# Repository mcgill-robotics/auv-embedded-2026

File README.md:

# McGill Robotics AUV Embedded 2026

Welcome to the AUV Embedded 2026 repository! This repository is created and maintained by the 2026 McGill Robotics AUV Electrical team. It serves as a platform for sharing, calibrating, and version-controlling the embedded software we develop for our Autonomous Underwater Vehicle (AUV).

## About Us

We are a dedicated team of students from McGill Robotics, focused on designing and implementing the PCBs and embedded systems that power our underwater robot. Our mission is to enable autonomous navigation and task performance through advanced electrical engineering and software development.

## What You'll Find Here

- **Embedded Software**: Source code and libraries for our AUV's embedded systems.
- **Team Structure**: Information about our team members and roles.
- **Tutorials**: Guides and tutorials on using ROS (Robot Operating System) and Arduino for our projects.

For more detail please visit our [Wiki](https://github.com/mcgill-robotics/auv-embedded-2026/wiki).

## Hydrophone related work 

You will find in the `dev/hydrophone` branch the following folders : 
- `documentation`, documenting the design of the new hydrophone ADC board. The documentation was written using _mkdocs_, and to view it you'll need to 1. clone the repository locally, then install mkdocs using `pip install mkdocs` and finally render the web documentation using `mkdocs serve` _in the `documentation` folder_
- `kicad`, which contains the source files (`ADC.kicad_pro`) for the design of the new ADC board
- `ltspice`, for the LTSPICE simulations of the ADC board signal chain.

If you have any questions regarding the hydrophone board design please contact @Oscar-T24

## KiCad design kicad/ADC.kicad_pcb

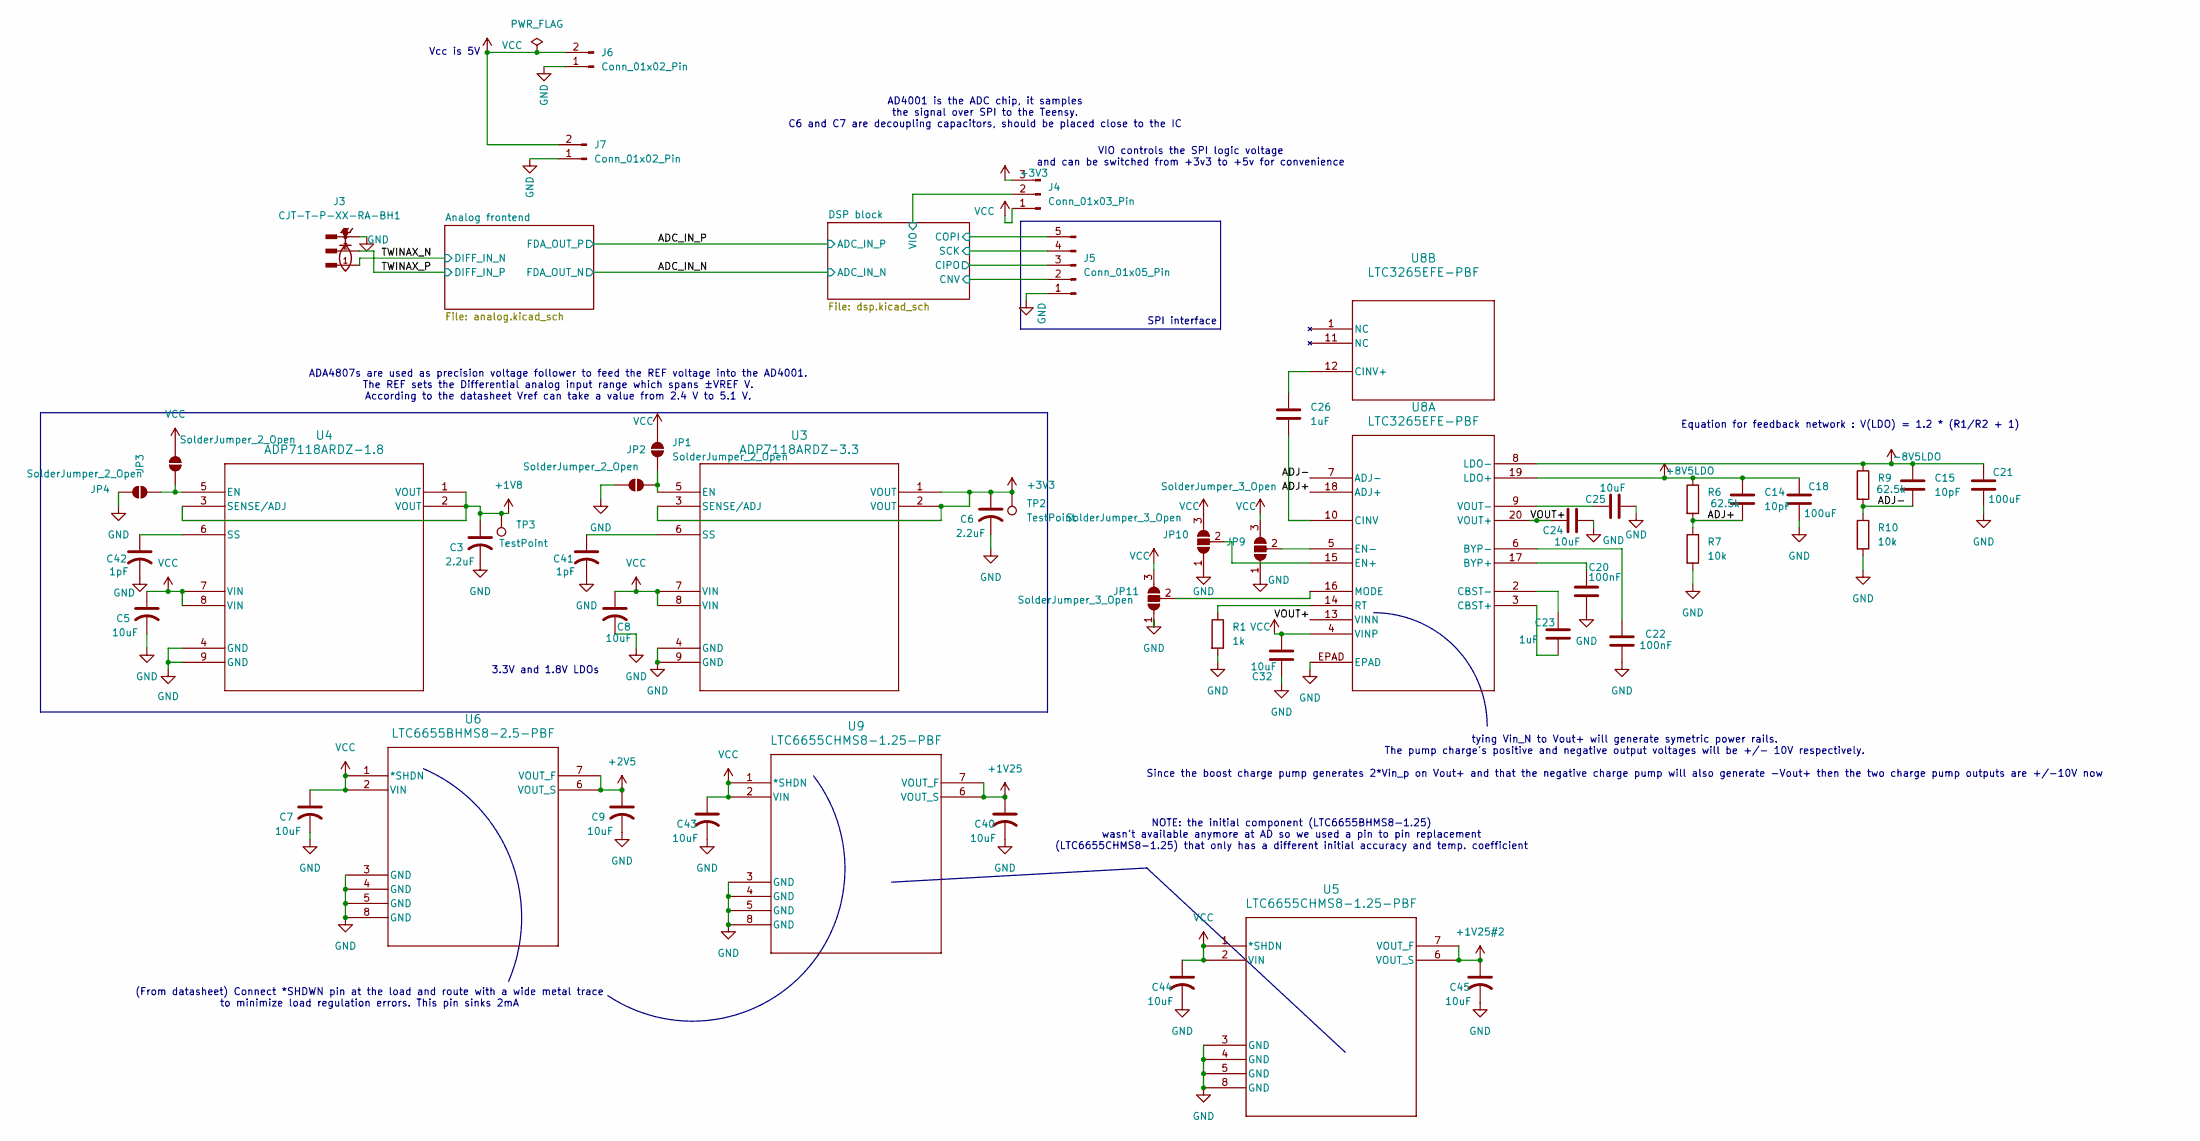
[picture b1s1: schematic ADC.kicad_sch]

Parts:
C3, C6: 2.2uF; C_0603_1608Metric_Pad1.08x0.95mm_HandSolder
C5, C7, C8, C9, C24, C25, C32, C40, C43, C44, C45: 10uF; C_0603_1608Metric_Pad1.08x0.95mm_HandSolder
C14, C15: 10pF; C_0603_1608Metric_Pad1.08x0.95mm_HandSolder
C18, C21: 100uF; C_1206_3216Metric_Pad1.33x1.80mm_HandSolder
C20, C22: 100nF; C_0603_1608Metric_Pad1.08x0.95mm_HandSolder
C23, C26: 1uF; C_0603_1608Metric_Pad1.08x0.95mm_HandSolder
C41, C42: 1pF; C_0603_1608Metric_Pad1.08x0.95mm_HandSolder
J3: CJT-T-P-XX-RA-BH1; SAMTEC_CJT-T-P-XX-RA-BH1; PARTREV E
J4: Conn_01x03_Pin; PinHeader_1x03_P2.54mm_Vertical
J5: Conn_01x05_Pin; PinHeader_1x05_P2.54mm_Vertical
J6, J7: Conn_01x02_Pin; PinHeader_1x02_P2.54mm_Vertical
JP1, JP2, JP3, JP4: SolderJumper_2_Open; SolderJumper-2_P1.3mm_Open_RoundedPad1.0x1.5mm
JP9, JP10, JP11: SolderJumper_3_Open; SolderJumper-3_P1.3mm_Open_RoundedPad1.0x1.5mm_NumberLabels
R1: 1k
R6, R9: 62.5k; R_0603_1608Metric_Pad0.98x0.95mm_HandSolder
R7, R10: 10k; R_0603_1608Metric_Pad0.98x0.95mm_HandSolder
TP2, TP3: TestPoint; TestPoint_Pad_D1.5mm
U3: ADP7118ARDZ-3.3; RD-8-1_ADI
U4: ADP7118ARDZ-1.8; RD-8-1_ADI
U5, U9: LTC6655CHMS8-1.25-PBF; MSOP-8_MS_LIT
U6: LTC6655BHMS8-2.5-PBF; MSOP-8_MS_LIT
U8: LTC3265EFE-PBF; FE_20_ADI

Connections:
+1V8: C3.1, TP3.1 (1_1), U4.1 (VOUT), U4.2 (VOUT), U4.3 (SENSE/ADJ); also elsewhere on the board
+1V25: C40.1, U9.6 (VOUT_S), U9.7 (VOUT_F); also elsewhere on the board
+1V25#2: C45.1, U5.6 (VOUT_S), U5.7 (VOUT_F); also elsewhere on the board
+2V5: C9.1, U6.6 (VOUT_S), U6.7 (VOUT_F); also elsewhere on the board
+3V3: C6.1, J4.3, TP2.1 (1_1), U3.1 (VOUT), U3.2 (VOUT), U3.3 (SENSE/ADJ)
+8V5LDO: C14.1, C18.1, R6.1, U8.19 (LDO+); also elsewhere on the board
-8V5LDO: C15.1, C21.1, R9.1, U8.8 (LDO-); also elsewhere on the board
/ADJ+: C14.2, R6.2, R7.1, U8.18 (ADJ+)
/ADJ-: C15.2, R9.2, R10.1, U8.7 (ADJ-)
/DSP block/CIPO: J5.3; also elsewhere on the board
/DSP block/CNV: J5.2; also elsewhere on the board
/DSP block/COPI: J5.5; also elsewhere on the board
/DSP block/SCK: J5.4; also elsewhere on the board
/DSP block/VIO: J4.2; also elsewhere on the board
/TWINAX_N: J3.1; also elsewhere on the board
/TWINAX_P: J3.2; also elsewhere on the board
/VOUT+: C24.1, U8.13 (VINN), U8.20 (VOUT+)
GND: C3.2, C5.2, C6.2, C7.2, C8.2, C9.2, C18.2, C20.2, C21.2, C22.2, C24.2, C25.2, C32.1, C40.2, C41.2, C42.2, C43.2, C44.2, C45.2, J3.3, J3.4, J3.5, J3.6, J5.1, J6.1, J7.1, JP2.2 (B), JP4.2 (B), JP9.1 (A), JP10.1 (A), JP11.1 (A), R1.2, R7.2, R10.2, U3.4 (GND), U3.9 (GND), U4.4 (GND), U4.9 (GND), U5.3 (GND), U5.4 (GND), U5.5 (GND), U5.8 (GND), U6.3 (GND), U6.4 (GND), U6.5 (GND), U6.8 (GND), U8.EPAD, U9.3 (GND), U9.4 (GND), U9.5 (GND), U9.8 (GND); also elsewhere on the board
unnamed: JP1.1 (A), JP2.1 (A), U3.5 (EN)
unnamed: JP3.2 (B), JP4.1 (A), U4.5 (EN)
unnamed: JP9.2 (C), U8.5 (EN-)
unnamed: JP10.2 (C), U8.15 (EN+)
unnamed: JP11.2 (C), U8.16 (MODE)
unnamed: C41.1, U3.6 (SS)
unnamed: C42.1, U4.6 (SS)
unnamed: C20.1, U8.17 (BYP+)
unnamed: C22.1, U8.6 (BYP-)
unnamed: C23.2, U8.3 (CBST+)
unnamed: C23.1, U8.2 (CBST-)
unnamed: C26.2, U8.10 (CINV)
unnamed: R1.1, U8.14 (RT)
unnamed: C25.1, U8.9 (VOUT-)
unnamed: C26.1, U8.12 (CINV+)
VCC: C5.1, C7.1, C8.1, C32.2, C43.1, C44.1, J4.1, J6.2, J7.2, JP1.2 (B), JP3.1 (A), JP9.3 (B), JP10.3 (B), JP11.3 (B), U3.7 (VIN), U3.8 (VIN), U4.7 (VIN), U4.8 (VIN), U5.1 (*SHDN), U5.2 (VIN), U6.1 (*SHDN), U6.2 (VIN), U8.4 (VINP), U9.1 (*SHDN), U9.2 (VIN); also elsewhere on the board

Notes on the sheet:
VIO controls the SPI logic voltage and can be switched from +3v3 to +5v for convenience
Vcc is 5V
(From datasheet) Connect *SHDWN pin at the load and route with a wide metal trace to minimize load regulation errors. This pin sinks 2mA
NOTE: the initial component (LTC6655BHMS8-1.25) wasn't available anymore at AD so we used a pin to pin replacement (LTC6655CHMS8-1.25) that only has a different initial accuracy and temp. coefficient
SPI interface
tying Vin_N to Vout+ will generate symetric power rails. The pump charge's positive and negative output voltages will be +/- 10V respectively. Since the boost charge pump generates 2*Vin_p on Vout+ and that the negative charge pump will also generate -Vout+ then the two charge pump outputs are +/-1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
Equation for feedback network : V(LDO) = 1.2 * (R1/R2 + 1)
ADA4807s are used as precision voltage follower to feed the REF voltage into the AD4001. The REF sets the Differential analog input range which spans ±VREF V. According to the datasheet Vref can take a value from 2.4 V to 5.1 V.
3.3V and 1.8V LDOs
AD4001 is the ADC chip, it samples the signal over SPI to the Teensy. C6 and C7 are decoupling capacitors, should be placed close to the IC

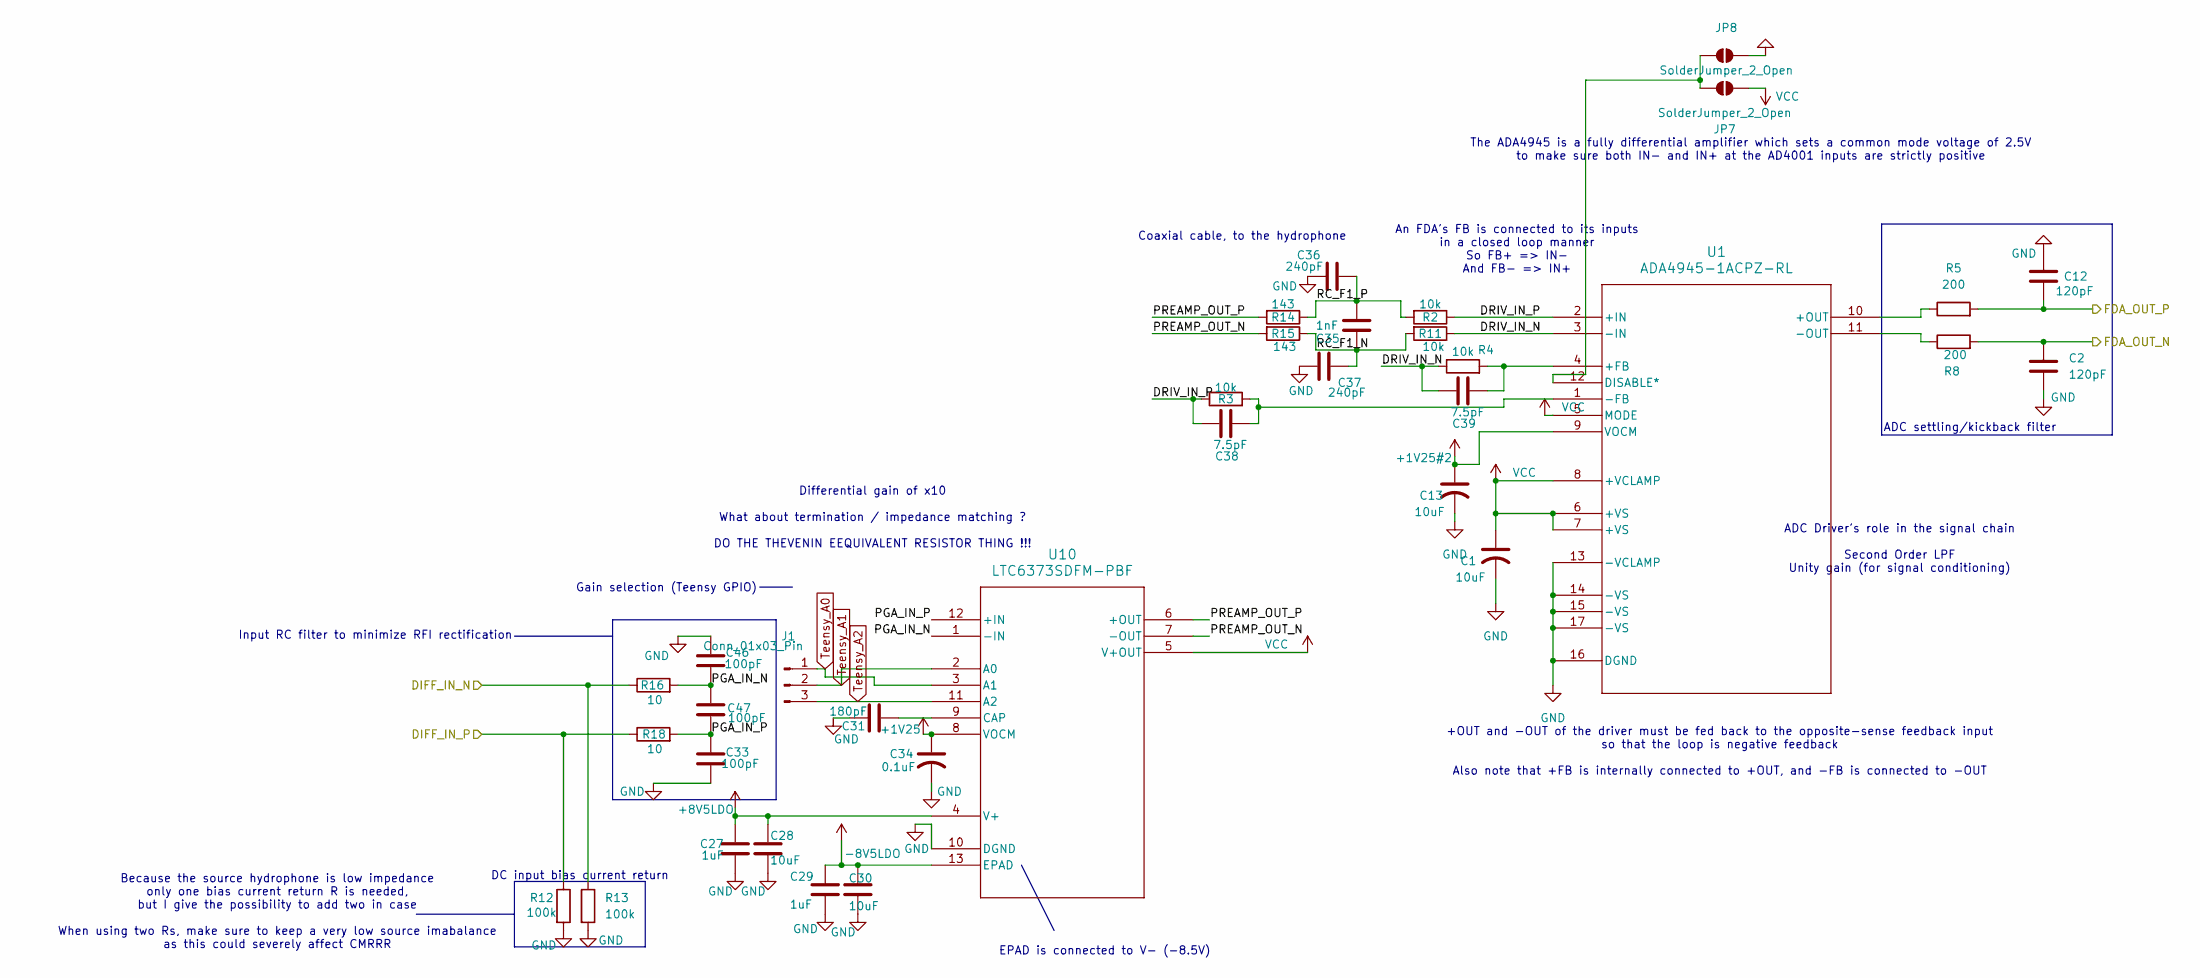
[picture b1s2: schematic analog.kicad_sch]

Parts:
C1, C13, C28, C30: 10uF; C_0603_1608Metric_Pad1.08x0.95mm_HandSolder
C2, C12: 120pF; C_0603_1608Metric_Pad1.08x0.95mm_HandSolder
C27, C29: 1uF; C_0603_1608Metric_Pad1.08x0.95mm_HandSolder
C31: 180pF; C_0603_1608Metric_Pad1.08x0.95mm_HandSolder
C33, C46, C47: 100pF; C_0603_1608Metric_Pad1.08x0.95mm_HandSolder
C34: 0.1uF; C_0603_1608Metric_Pad1.08x0.95mm_HandSolder
C35: 1nF; C_0603_1608Metric_Pad1.08x0.95mm_HandSolder
C36, C37: 240pF; C_0603_1608Metric_Pad1.08x0.95mm_HandSolder
C38, C39: 7.5pF; C_0603_1608Metric_Pad1.08x0.95mm_HandSolder
J1: Conn_01x03_Pin; PinHeader_1x03_P2.54mm_Vertical
JP7, JP8: SolderJumper_2_Open
R2, R3, R4, R11: 10k; R_0603_1608Metric_Pad0.98x0.95mm_HandSolder
R5, R8: 200; R_0603_1608Metric_Pad0.98x0.95mm_HandSolder
R12, R13: 100k; R_0603_1608Metric_Pad0.98x0.95mm_HandSolder
R14, R15: 143; R_0603_1608Metric_Pad0.98x0.95mm_HandSolder
R16, R18: 10; R_0603_1608Metric_Pad0.98x0.95mm_HandSolder
U1: ADA4945-1ACPZ-RL; LFCSP16_ADA4945-1ACPZ-R2_ADI
U10: LTC6373SDFM-PBF; 05-08-1791_ADI

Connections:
+1V25: C34.1, U10.8 (VOCM); also elsewhere on the board
+1V25#2: C13.1, U1.9 (VOCM); also elsewhere on the board
+8V5LDO: C27.1, C28.1, U10.4 (V+); also elsewhere on the board
-8V5LDO: C29.1, C30.1, U10.13 (EPAD); also elsewhere on the board
/ADC_IN_N: C2.1, R8.2; also elsewhere on the board
/ADC_IN_P: C12.2, R5.2; also elsewhere on the board
/Analog frontend/DRIV_IN_N: C39.2, R4.1, R11.1, U1.3 (-IN)
/Analog frontend/DRIV_IN_P: C38.2, R2.1, R3.1, U1.2 (+IN)
/Analog frontend/PGA_IN_N: C46.1, C47.2, R16.2, U10.1 (-IN)
/Analog frontend/PGA_IN_P: C33.2, C47.1, R18.2, U10.12 (+IN)
/Analog frontend/PREAMP_OUT_N: R15.2, U10.7 (-OUT)
/Analog frontend/PREAMP_OUT_P: R14.2, U10.6 (+OUT)
/Analog frontend/RC_F1_N: C35.1, C37.1, R11.2, R15.1
/Analog frontend/RC_F1_P: C35.2, C36.1, R2.2, R14.1
/TWINAX_N: R13.1, R16.1; also elsewhere on the board
/TWINAX_P: R12.1, R18.1; also elsewhere on the board
GND: C1.2, C2.2, C12.1, C13.2, C27.2, C28.2, C29.2, C30.2, C31.1, C33.1, C34.2, C36.2, C37.2, C46.2, JP8.1 (A), R12.2, R13.2, U1.13 (-VCLAMP), U1.14 (-VS), U1.15 (-VS), U1.16 (DGND), U1.17 (-VS), U10.10 (DGND); also elsewhere on the board
unnamed: JP7.2 (B), JP8.2 (B), U1.12 (DISABLE*)
unnamed: C39.1, R4.2, U1.4 (+FB)
unnamed: R5.1, U1.10 (+OUT)
unnamed: C38.1, R3.2, U1.1 (-FB)
unnamed: R8.1, U1.11 (-OUT)
unnamed: C31.2, U10.9 (CAP)
Teensy_A0: J1.1, U10.3 (A1)
Teensy_A1: J1.2, U10.2 (A0)
Teensy_A2: J1.3, U10.11 (A2)
VCC: C1.1, JP7.1 (A), U1.5 (MODE), U1.6 (+VS), U1.7 (+VS), U1.8 (+VCLAMP), U10.5 (V+OUT); also elsewhere on the board

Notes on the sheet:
ADC Driver's role in the signal chain Second Order LPF Unity gain (for signal conditioning)
An FDA's FB is connected to its inputs in a closed loop manner So FB+ => IN- And FB- => IN+
+OUT and -OUT of the driver must be fed back to the opposite-sense feedback input so that the loop is negative feedback Also note that +FB is internally connected to +OUT, and -FB is connected to -OUT
ADC settling/kickback filter
Gain selection (Teensy GPIO)
DC input bias current return
Differential gain of x10 What about termination / impedance matching ? DO THE THEVENIN EEQUIVALENT RESISTOR THING !!!
Because the source hydrophone is low impedance only one bias current return R is needed, but I give the possibility to add two in case When using two Rs, make sure to keep a very low source imabalance as this could severely affect CMRRR
Coaxial cable, to the hydrophone
EPAD is connected to V- (-8.5V)
Input RC filter to minimize RFI rectification
The ADA4945 is a fully differential amplifier which sets a common mode voltage of 2.5V to make sure both IN- and IN+ at the AD4001 inputs are strictly positive

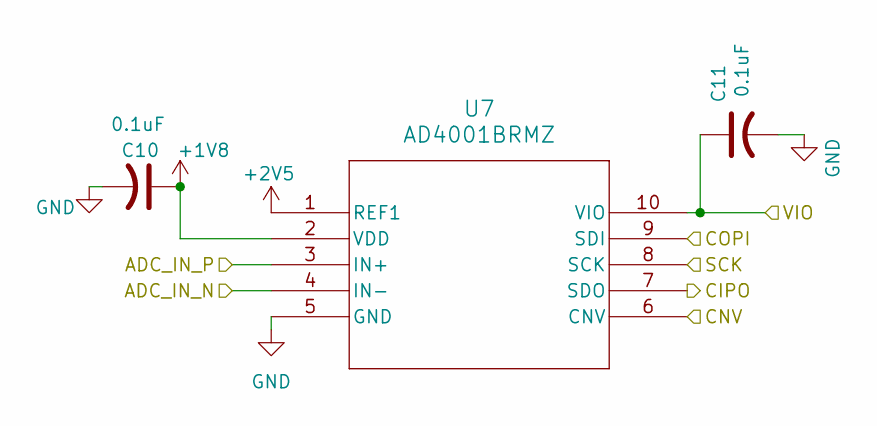
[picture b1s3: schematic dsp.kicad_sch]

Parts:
C10, C11: 0.1uF; C_0603_1608Metric_Pad1.08x0.95mm_HandSolder
U7: AD4001BRMZ; RM_10_ADI-L

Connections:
+1V8: C10.1, U7.2 (VDD); also elsewhere on the board
+2V5: U7.1 (REF1); also elsewhere on the board
/ADC_IN_N: U7.4 (IN-); also elsewhere on the board
/ADC_IN_P: U7.3 (IN+); also elsewhere on the board
/DSP block/CIPO: U7.7 (SDO); also elsewhere on the board
/DSP block/CNV: U7.6 (CNV); also elsewhere on the board
/DSP block/COPI: U7.9 (SDI); also elsewhere on the board
/DSP block/SCK: U7.8 (SCK); also elsewhere on the board
/DSP block/VIO: C11.1, U7.10 (VIO); also elsewhere on the board
GND: C10.2, C11.2, U7.5 (GND); also elsewhere on the board

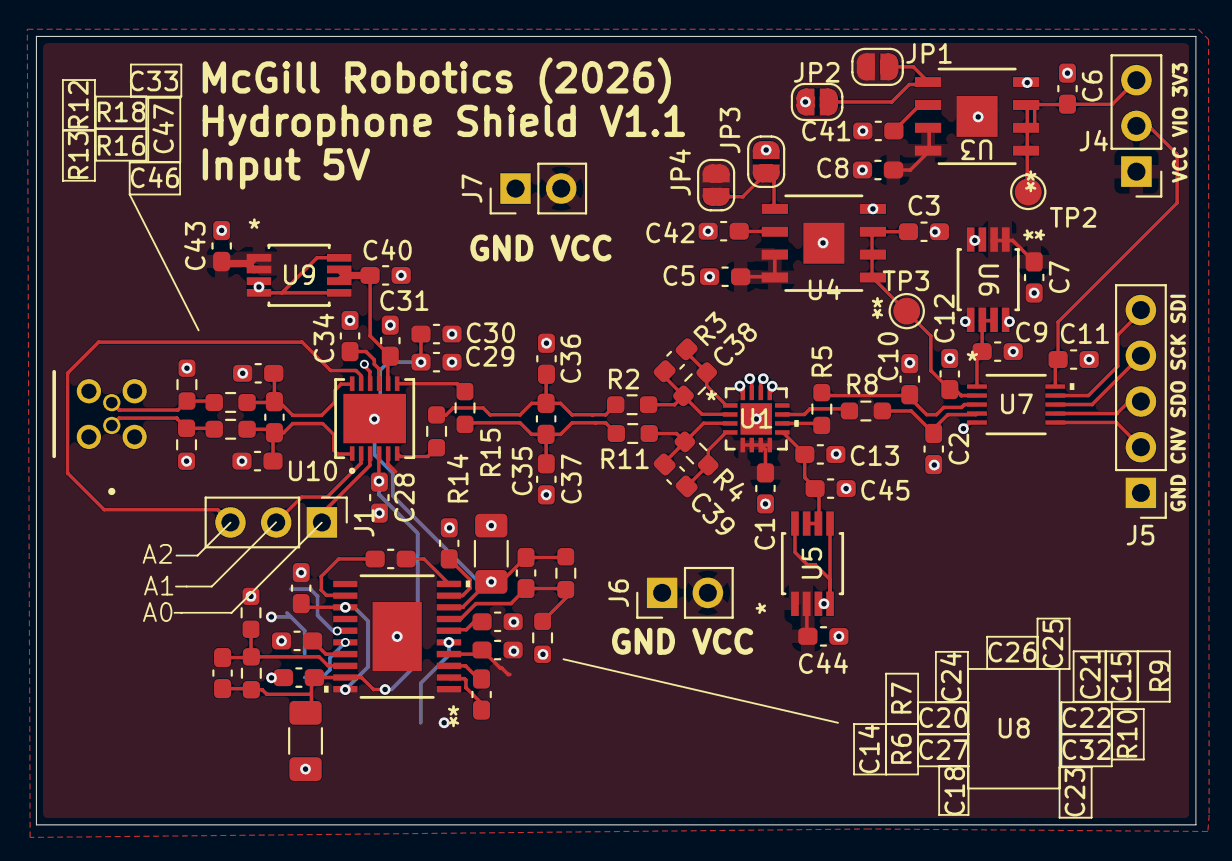
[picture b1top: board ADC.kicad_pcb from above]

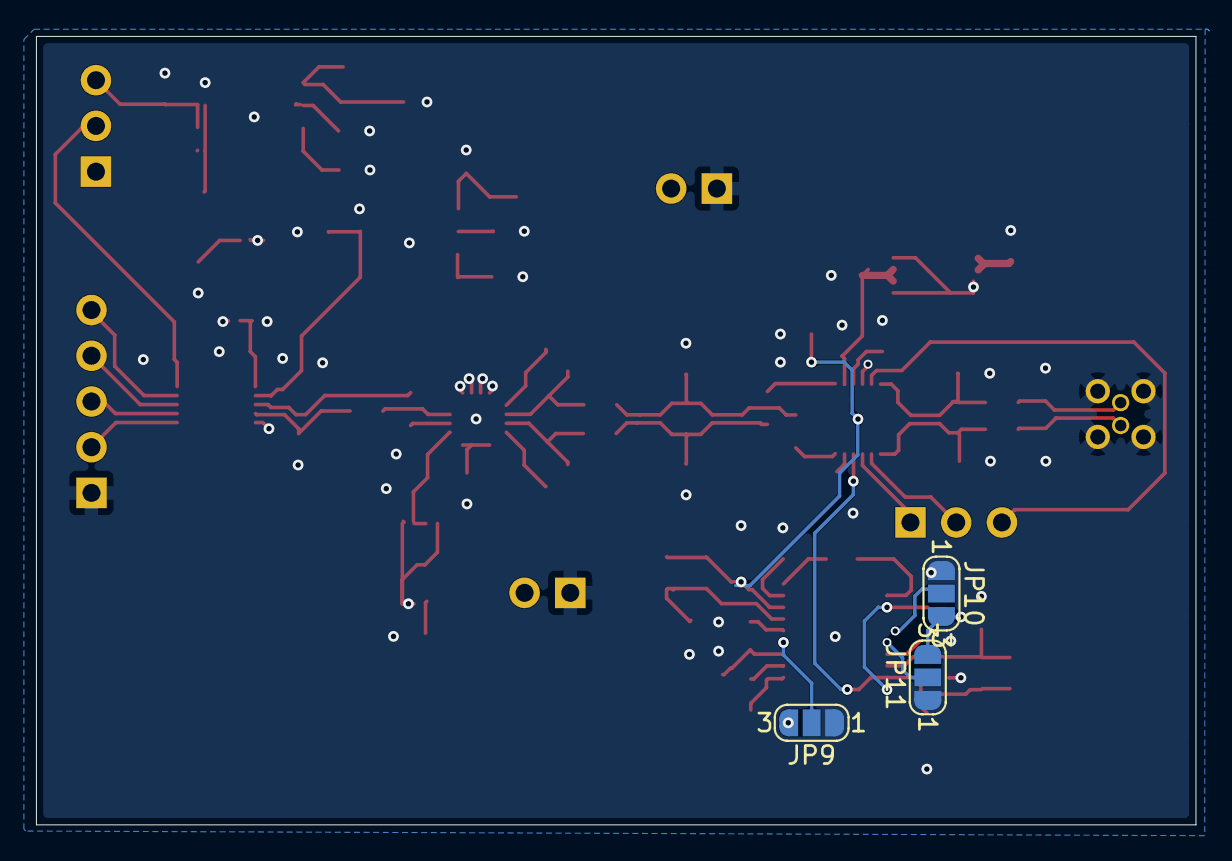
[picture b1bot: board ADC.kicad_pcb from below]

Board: 2 copper layers, 64.4 x 43.8 mm, 83 parts (3 on the bottom side), 51 nets.

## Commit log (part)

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2025-09-11 Updated platformio-ci.yml to reduce CI/CD schedule to once (1) a day
    this is just better
2025-09-16 2025 wiki archive
2025-09-16 Update README.md
    changed 2025 to 2026
2025-10-06 fixed battery voltage text color from white to black, hopefully it works
2025-10-18 Updated ros_lib library
2025-10-18 Second sync of custom messages
2025-10-25 optimizing display code to make depth sensor more efficient with depth_sensor_opti.cpp
2025-11-01 Rearrange thruster pin definitions
2025-11-01 Remove @andrew-kan from CODEOWNERS
    bye bye andrew <3
2025-11-08 new actuator ROS2 file
2025-11-08 added new header file
2025-11-08 included ROS 2 actuator env in platform.io
2025-11-08 fixed syntax errors for main.cpp
2025-11-17 adding actuator ROS2 file
2025-11-17 added header
2025-11-24 fixed, missing references in ros2
2025-11-25 finished ros2 code for actuator
2025-11-29 First Version of Depth Sensor Code in ROS2
2025-11-29 shifted and moved display ros 2 code with env and, headers, and renamed original code -- to be tested with real display board. builds successfully
2025-12-01 Refactor power_main.cpp and improve safety checks, sending 1500us to thrusters at shutdown from thurster ks or any shutdown
    Refactored error_loop and callback functions, added initialization for microseconds array on reset, and ensured safety before destroying entities.
    In power_setup() (line ~242): Initializes the microseconds array immediately after the message buffer initialization. This ensures that when the Teensy resets (kill switch pulled/reinserted), the thr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
    In create_entities() (line ~155): Resets the microseconds array when ROS entities are created/reconnected. This handles the case where the ROS node on your ho
2025-12-02 created a failsafe such that after a time interval, it will automatically rearm the thrusters to 1500us. This means that if one crashes a CLI publisher node, it will actually rearm the thrusters corr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
2026-01-07 Create README.md for AUV Embedded 2026 project
    Added a README file for the AUV Embedded 2026 project, detailing the team, software, and resources available.
2026-01-07 Revise README for source code overview and clarity
    Updated the README to provide a clearer overview of the source code and its purpose, while removing outdated sections.
2026-01-08 updated code to remove LED pin - it works
2026-01-08 put a formula - works fully and funny
2026-01-08 Update README with depth sensor publishing details
    Clarified the description of the depth sensor publishing rate and added examples for timer timeout calculations.
2026-01-08 display_main.cpp aktualisieren; removed counter -works
2026-01-15 adding deps and removing url
2026-01-15 grammar and naming changes
2026-01-15 added the display ros1 setup and loop to main
2026-01-15 standardized function names and fixed conflicts
2026-01-17 setup for water detection, IRQ to be implemented
2026-01-18 Update README.md
    Disclaimer about ROS1 and formatting
2026-01-24 tester code for KS pin (ONLY FOR TESTING PURPOSES)
2026-01-28 setup code for leaving ks pin floating until pull to low, need to physically connect 3.3V
2026-02-07 test code for water and ks combo
2026-02-21 Added blocking loop to ensure depth sensor is initialized
2026-02-21 Changed output frequency to 15Hz
2026-02-22 Fixed bug, secured a failsafe for thrusters
    Previous logic kept updating the thrusters to the old values even after disconnecting.
2026-02-22 Automatic formatting for cpp
2026-02-22 Revert "Automatic formatting for cpp"
    This reverts commit 56b727b147b465422d80401d80d87830f5aabc53.
2026-02-22 Merged updateThrusters updates within switch case and reordered function call in detroy_entities
2026-03-02 decrease killing latency
2026-03-02 Feat: pinModeOutputHigh, preloads output pin with HIGH
2026-03-02 Basic undervoltage voltage detection, system KS toggling
2026-03-03 typo in comment
2026-03-03 Update platformio.ini to prevent arm errors for display
2026-03-03 Update platformio-ci.yml to support amd and arm builds
2026-03-03 rename state to microros_state
2026-03-03 repo library cleanup
2026-03-03 Added power state machine
2026-03-03 Update custom_cores.cpp to remove irrelevant comment from original teensy cores
2026-03-03 Remove STARTUP state from power_states enum
2026-03-06 adding display code with no ros in it
2026-03-06 testing display code with no ros in it
2026-03-13 Added python files to stream hydrophone data to Jetson board
2026-03-19 Added recordng scripts
2026-03-19 final testing
2026-03-19 naming convention
2026-03-27 first ros2 and finl serial code for display done
2026-03-30 Changed depth publishing frequency to 67
2026-03-30 fixed ros2 issues, more to debug concerning frequency and delays check lines 797-798 and trusters are bugging as well
2026-06-13 torpedo testing
2026-06-13 speedmaxxing
2026-06-13 organizemaxxing
2026-06-16 Basic ros implementation, lags when publishing
2026-06-16 cleanupmaxxing
2026-06-20 Update actuator torpedo topic name
2026-06-23 grabbermaxxing
2026-06-23 grabber with ros to be tested
2026-06-23 added KiCad files and refactored Kicad imports to be encapsulated into the project working directory
2026-06-23 updated documentation
2026-06-24 to be tested
2026-06-24 commentmaxxing
